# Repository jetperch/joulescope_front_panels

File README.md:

# Joulescope Front Panels

Welcome to Joulescope™ front panel hardware design project.  This project 
contains the open source hardware designs for a variety of Joulescope front
panels.  These front panels customize Joulescope so that it can more easily 
connect to your power supply and target device.
For more information on Joulescope, see 
[www.joulescope.com](https://www.joulescope.com).

As of Mar 2019, all designs were done in Autodesk Eagle PCB.

The [Baseline PDF](fp_baseline.pdf) show the board outline and critical 
dimensions.

The boards have been fabricated using PCBWay. 
Here are the order notes ([example](pcbway_order.png)):

* Size: 77.6 x 26.6 mm
* Solder Mask: Black
* Surface Finish: HASL lead free, yes to accept ENIG substitution
* Special requests: Place all markings (such as pcb order number) on back.  Add flammability rating marking, such as 94V-0.

## License

All Joulescope front-panel designs are released under the 
permissive Apache 2.0 license.

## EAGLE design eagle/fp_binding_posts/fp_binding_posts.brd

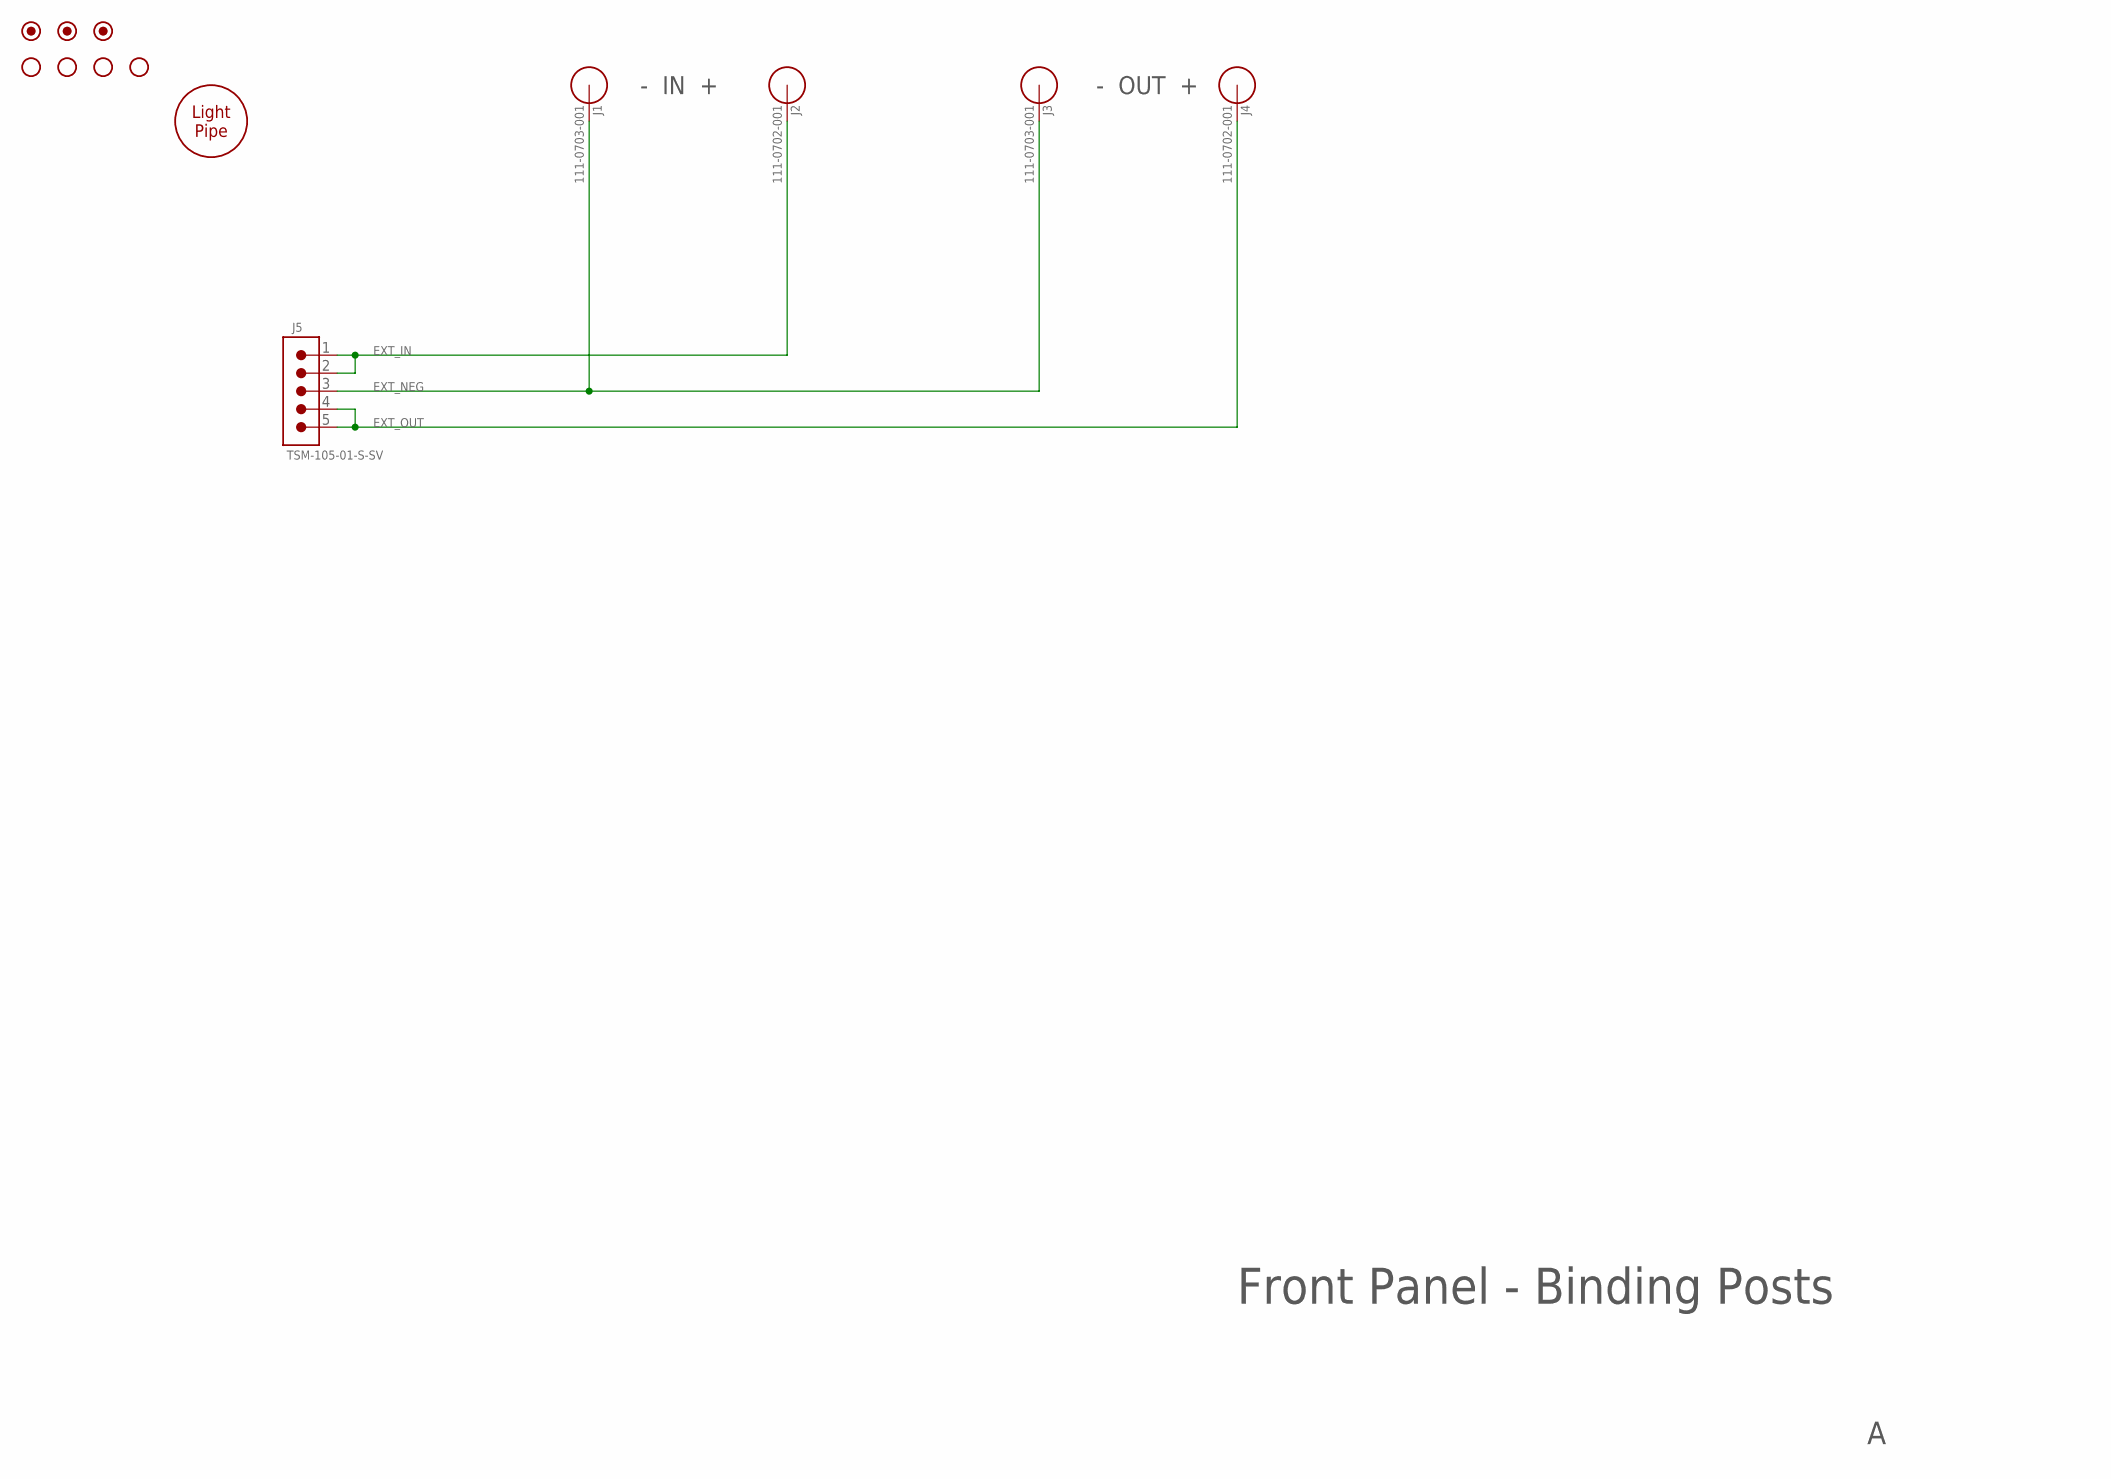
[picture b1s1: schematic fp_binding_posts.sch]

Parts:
FUD1, FUD2, FUD3: FIDUCIAL_1MM; FIDUCIAL_1MM_2MM
H1: 51513020125F; LP_3MM; MPN 51513020125F
H2, H3, H4, H5: HOLE_#6; HOLE_3.5MM
J1, J3: 111-0703-001; BINDING_POST_6
J2, J4: 111-0702-001; BINDING_POST_6
J5: TSM-105-01-S-SV; CONN_0.1_5X1_MS; MPN TSM-105-01-S-SV

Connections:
EXT_IN: J2.1, J5.1, J5.2
EXT_NEG: J1.1, J3.1, J5.3
EXT_OUT: J4.1, J5.4, J5.5

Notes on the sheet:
Front Panel - Binding Posts
- IN +
- OUT +

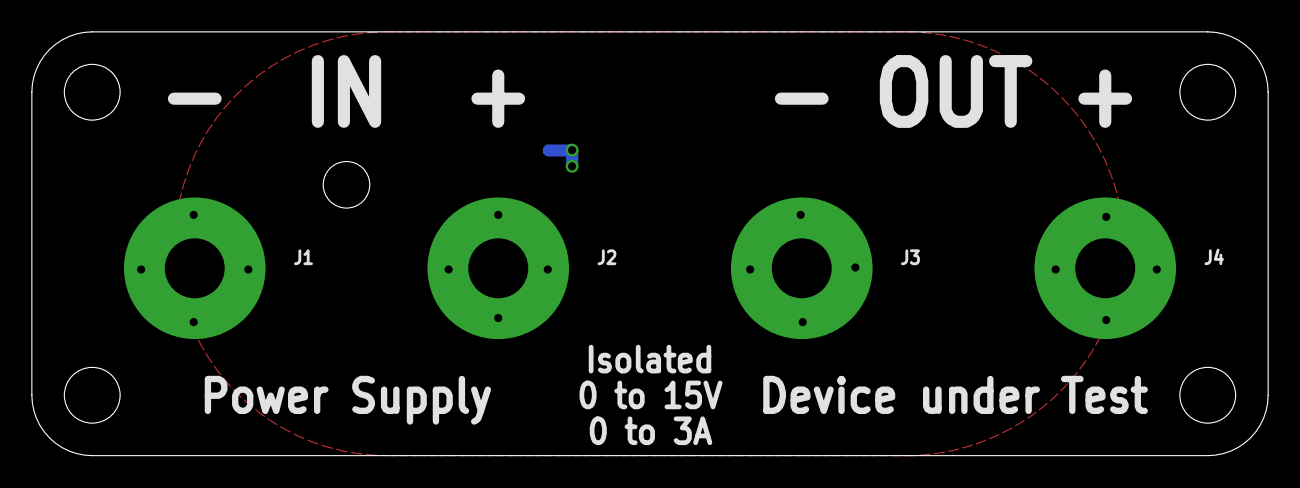
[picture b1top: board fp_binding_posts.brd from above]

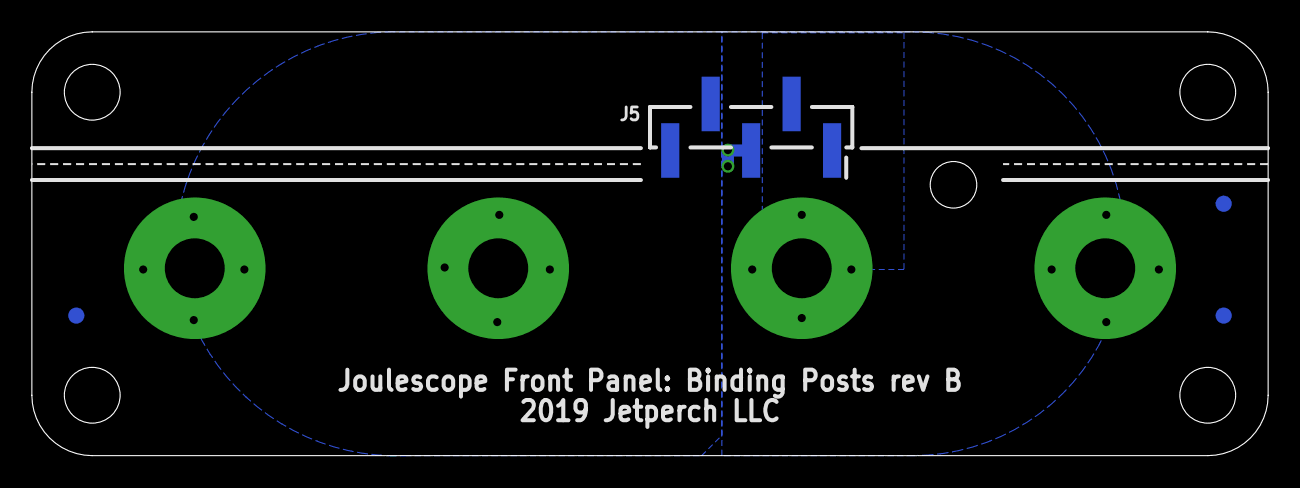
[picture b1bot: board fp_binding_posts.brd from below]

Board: 2 copper layers, 77.6 x 26.6 mm, 13 parts (4 on the bottom side), 3 nets.

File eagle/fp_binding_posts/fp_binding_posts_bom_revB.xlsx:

Binding Post Front Panel BOM - rev B
2019 June 10
# | Ref Des | Qty | Package | Description | Mfg | Mfg Part # | Notes
1 | J2, J4 | 2 |  | Binding post - red | Cinch | 111-0702-001
2 | J1, J3 | 2 |  | Binding post - black | Cinch | 111-0703-001
3 | J5 | 1 | 0.1" 1x5 SM | Surface mount header | Samtec | TSM-105-01-S-SV
4 | H1 | 1 |  | Light pipe | Dialight | 51513020125F

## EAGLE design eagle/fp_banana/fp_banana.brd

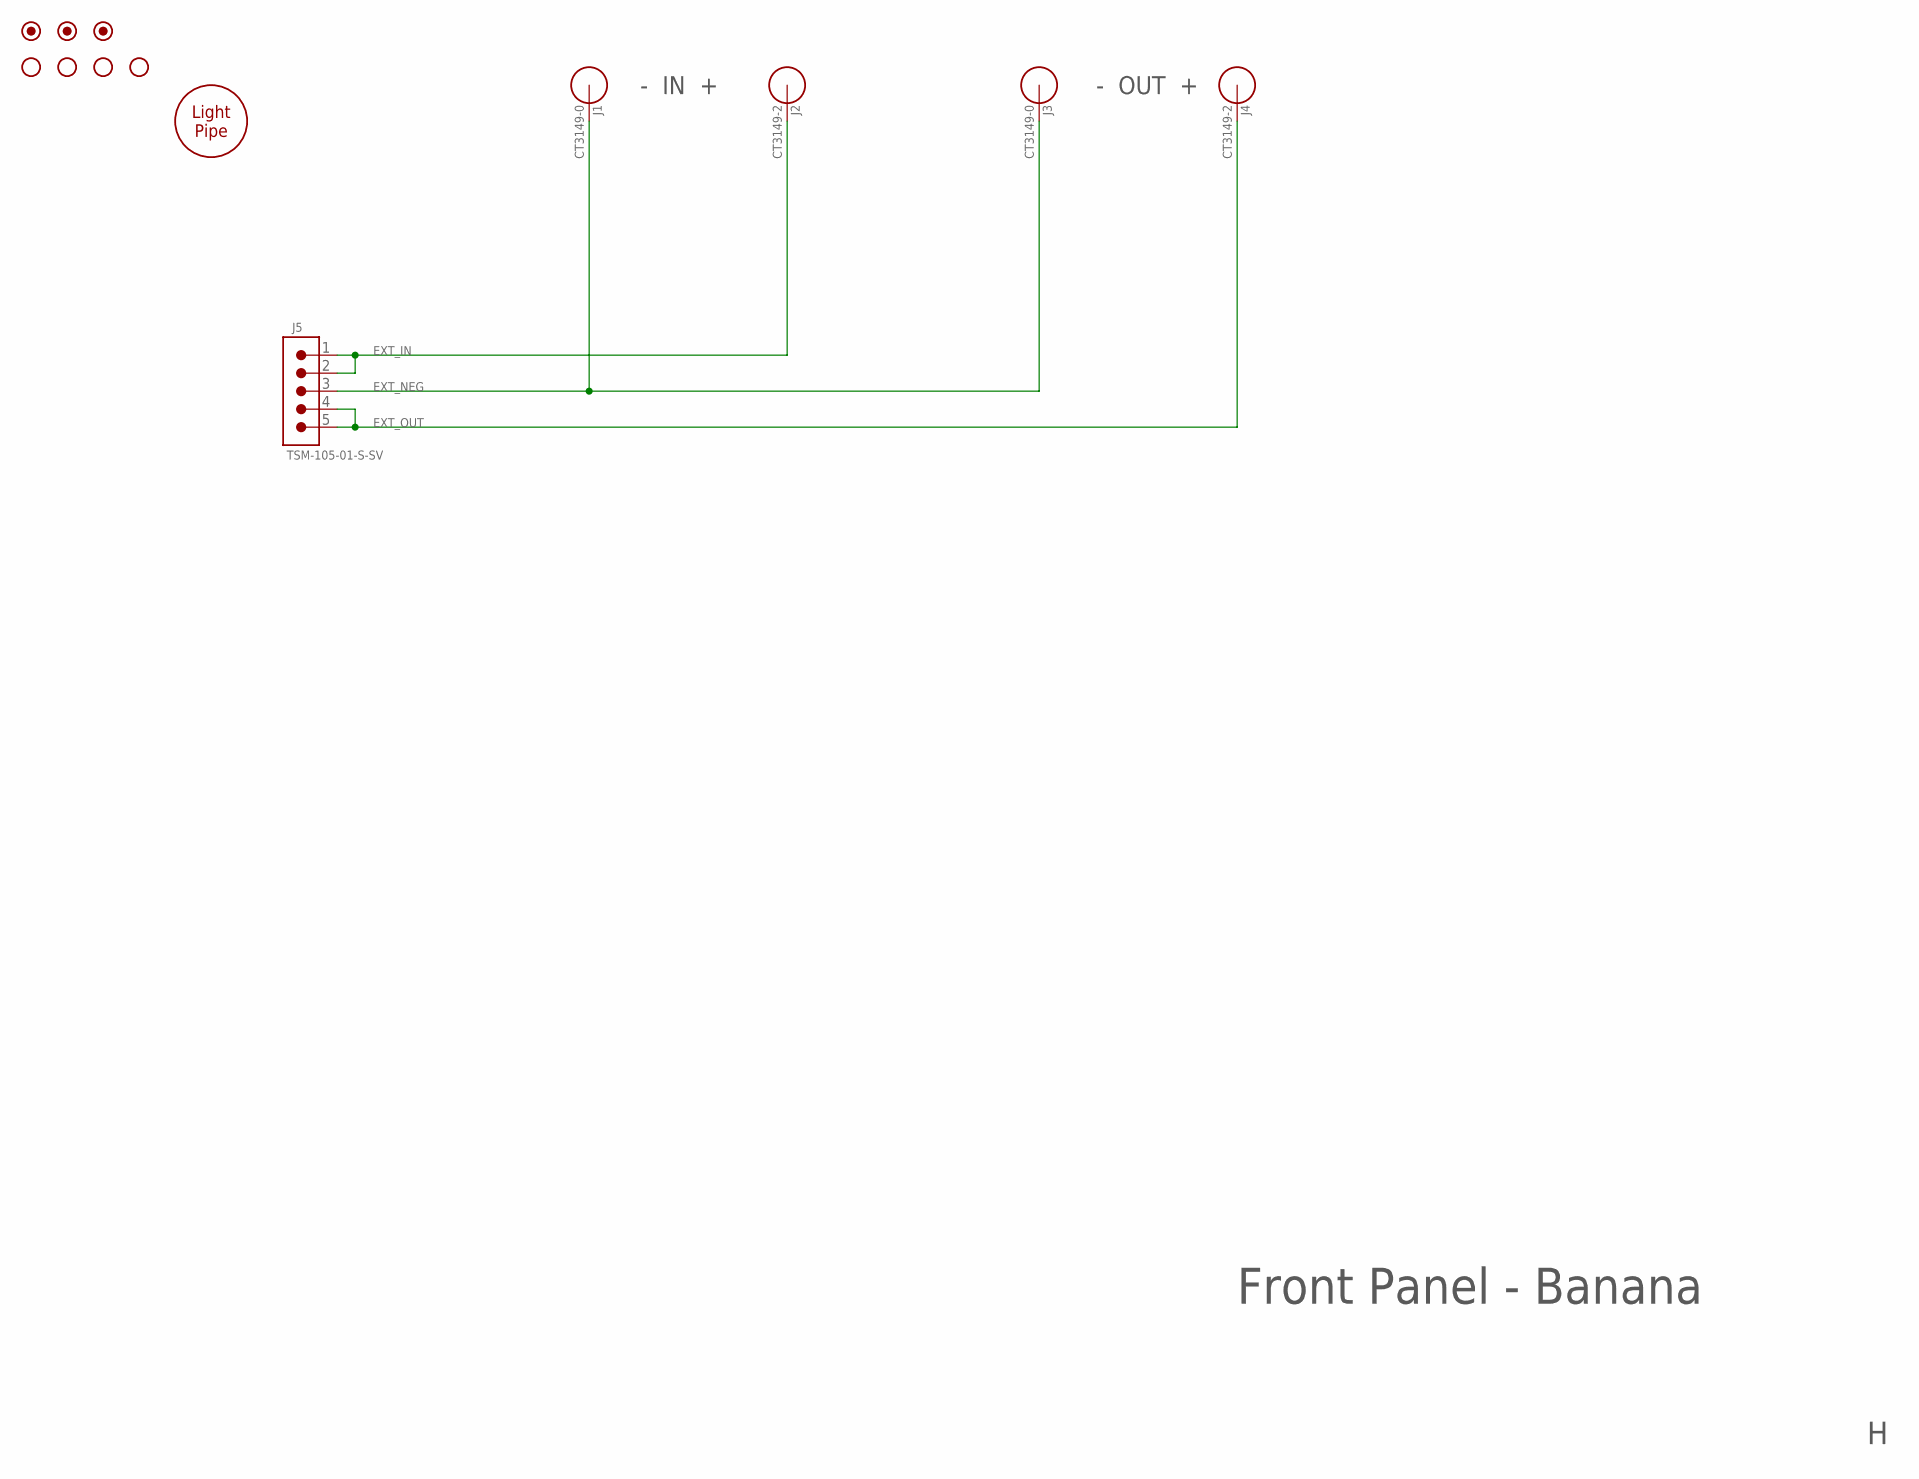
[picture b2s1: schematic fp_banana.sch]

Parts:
FUD1, FUD2, FUD3: FIDUCIAL_1MM; FIDUCIAL_1MM_2MM
H1: 51513020125F; LP_3MM; MPN 51513020125F
H2, H3, H4, H5: HOLE_#6; HOLE_3.5MM
J1, J3: CT3149-0; CT3149
J2, J4: CT3149-2; CT3149
J5: TSM-105-01-S-SV; CONN_0.1_5X1_MS; MPN TSM-105-01-S-SV

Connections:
EXT_IN: J2.A, J5.1, J5.2
EXT_NEG: J1.A, J3.A, J5.3
EXT_OUT: J4.A, J5.4, J5.5

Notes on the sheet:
Front Panel - Banana
- IN +
- OUT +

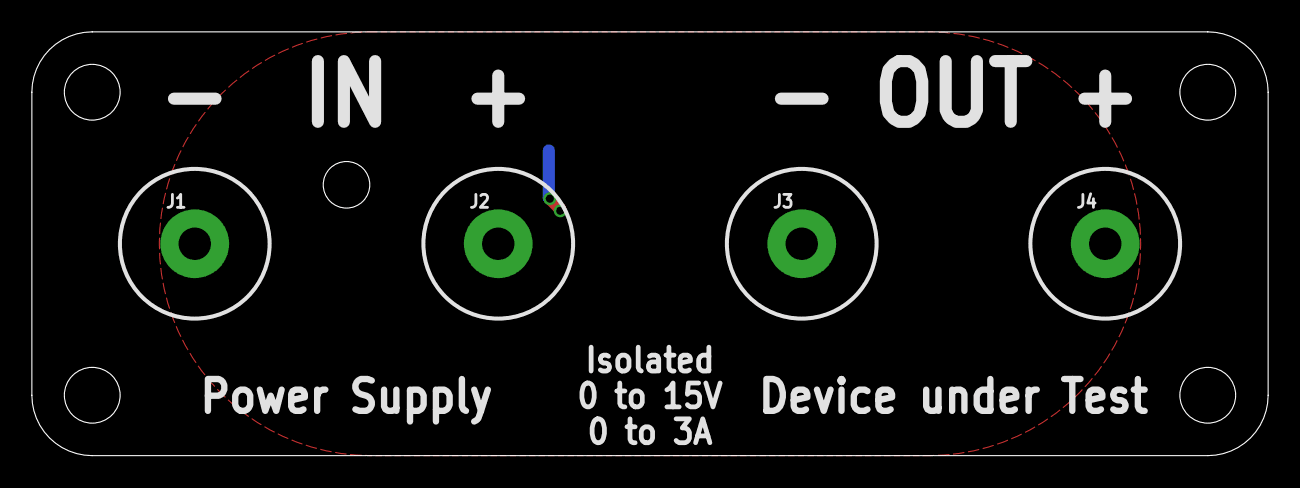
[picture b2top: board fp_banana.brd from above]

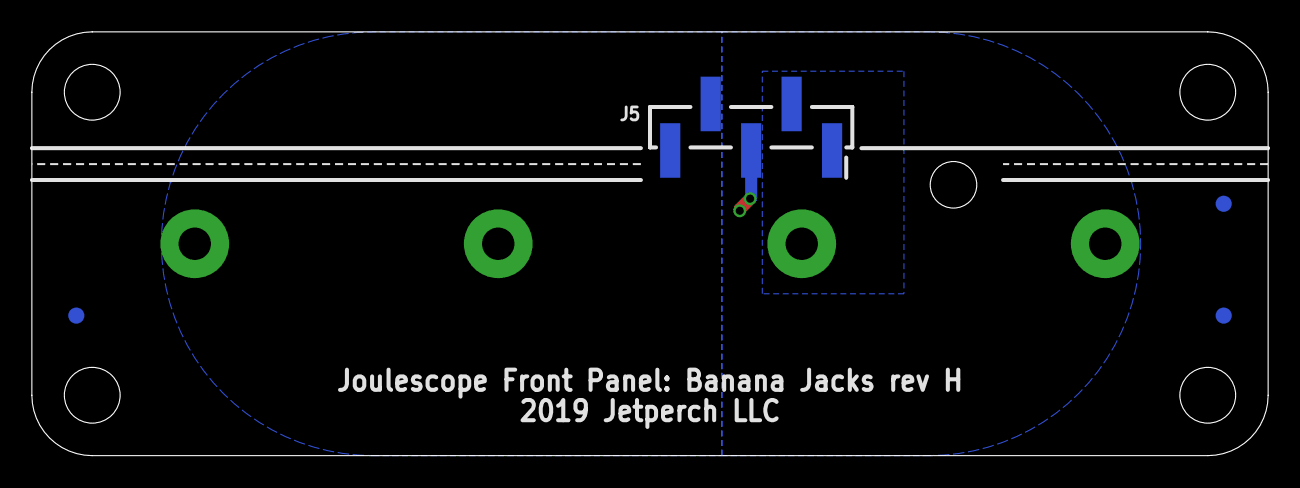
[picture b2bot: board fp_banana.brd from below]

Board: 2 copper layers, 77.6 x 26.6 mm, 13 parts (4 on the bottom side), 3 nets.

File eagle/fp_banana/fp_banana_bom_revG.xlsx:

Banana Jack Front Panel BOM - Rev G
2019 June 10
# | Ref Des | Qty | Value | Package | Description | Mfg | Mfg Part # | Notes
1 | J1, J3 | 2 |  |  | Safety banana jack - black | Cal Test | CT3149-0
2 | J2, J4 | 2 |  |  | Safety banana jack - red | Cal Test | CT3149-2
3 | J5 | 1 |  | 0.1" 1x5 SM | Surface mount header | Samtec | TSM-105-01-S-SV
4 | H1 | 1 |  |  | Light pipe | Dialight | 51513020125F
5 |  | 1 |  |  | PCB | PCBWay | W40090AXN58

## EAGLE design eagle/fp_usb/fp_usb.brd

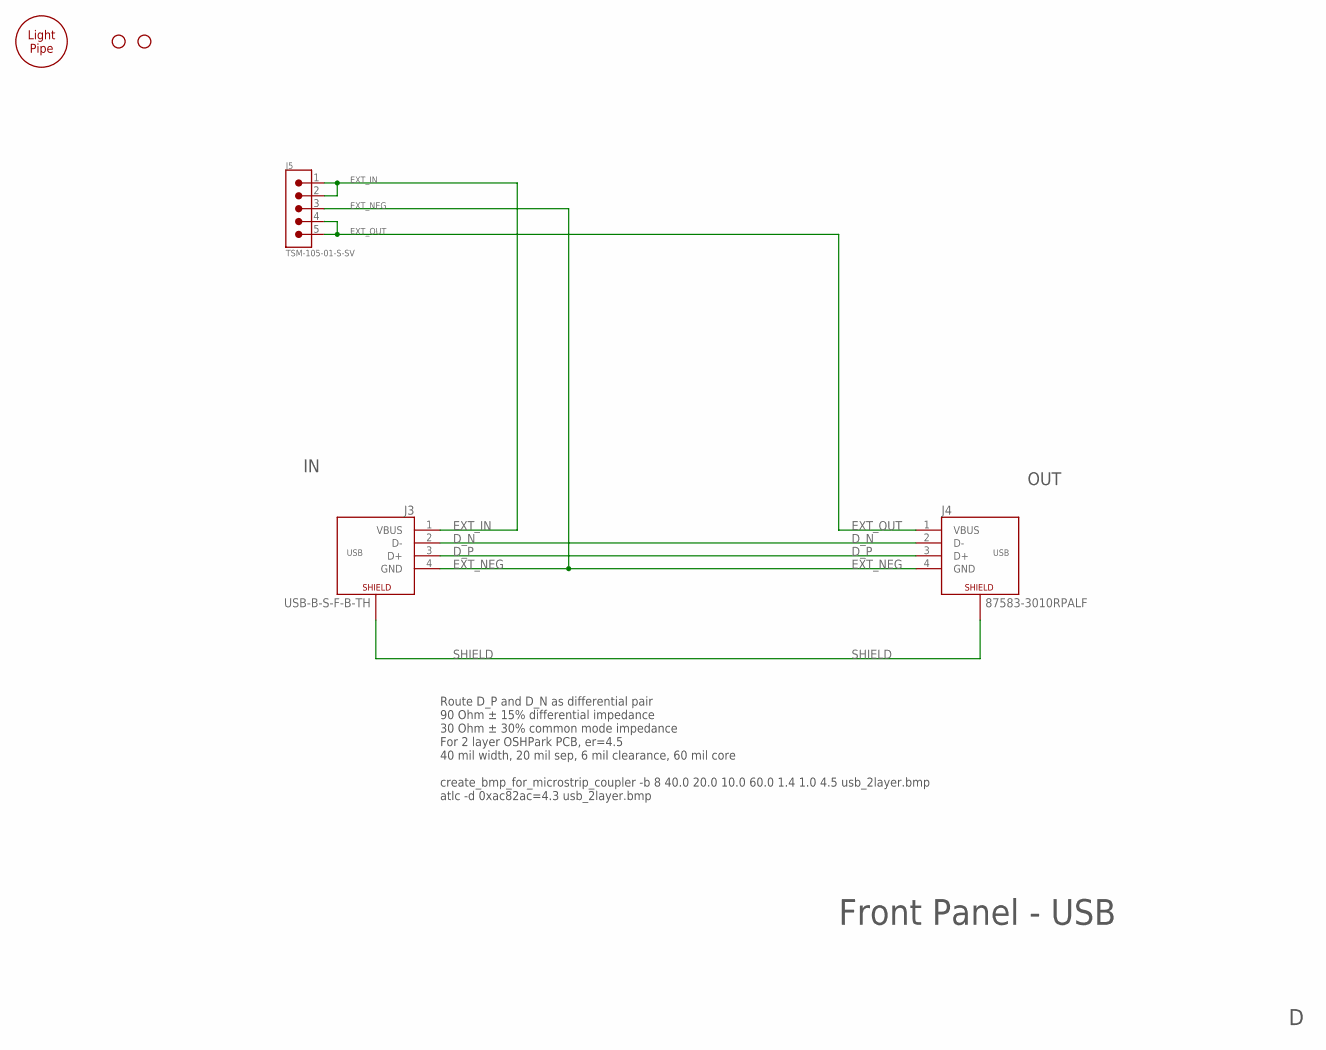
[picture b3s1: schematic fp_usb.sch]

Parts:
H1: 51513020125F; LP_3MM; MPN 51513020125F
H3, H4: HOLE_#6; HOLE_3.5MM
J3: USB-B-S-F-B-TH; USB-B-TH; MPN USB-B-S-F-B-TH
J4: 87583-3010RPALF; USB-A_RPCT; MPN 87583-3010RPALF
J5: TSM-105-01-S-SV; CONN_0.1_5X1_MS; MPN TSM-105-01-S-SV

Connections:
D_N: J3.2 (D-), J4.2 (D-)
D_P: J3.3 (D+), J4.3 (D+)
EXT_IN: J3.1 (VBUS), J5.1, J5.2
EXT_NEG: J3.4 (GND), J4.4 (GND), J5.3
EXT_OUT: J4.1 (VBUS), J5.4, J5.5
SHIELD: J3.SHIELD@1 (SHIELD), J3.SHIELD@2 (SHIELD), J4.SHIELD@1 (SHIELD), J4.SHIELD@2 (SHIELD)

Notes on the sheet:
Front Panel - USB
OUT
Route D_P and D_N as differential pair 90 Ohm ± 15% differential impedance 30 Ohm ± 30% common mode impedance For 2 layer OSHPark PCB, er=4.5 40 mil width, 20 mil sep, 6 mil clearance, 60 mil core create_bmp_for_microstrip_coupler -b 8 40.0 20.0 10.0 60.0 1.4 1.0 4.5 usb_2layer.bmp atlc -d 0xac82ac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

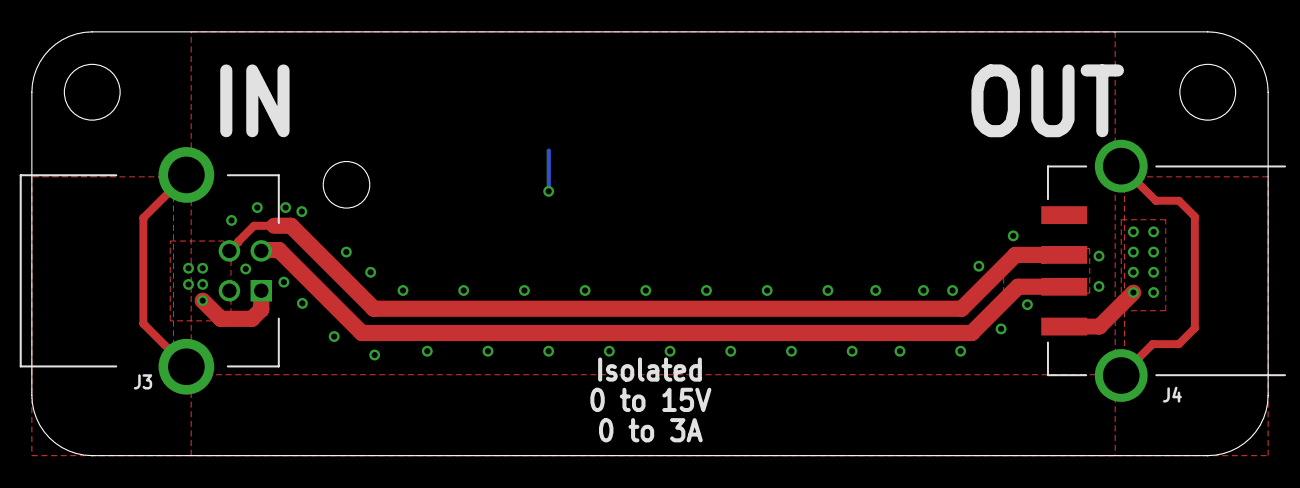
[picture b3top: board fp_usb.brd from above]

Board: 2 copper layers, 77.6 x 26.6 mm, 6 parts (1 on the bottom side), 6 nets.

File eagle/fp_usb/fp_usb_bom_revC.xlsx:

USB Front Panel BOM - rev C
2019 June 10
# | Ref Des | Qty | Value | Package | Description | Mfg | Mfg Part # | Notes
1 | J5 | 1 |  | 0.1" 1x5 SM | Surface mount header | Samtec | TSM-105-01-S-SV
2 | J3 | 1 |  |  | USB B connector | Samtec | USB-B-S-F-B-TH
3 | J4 | 1 |  |  | USB A connector | Amphenol | 87583-3010RPALF
4 | H1 | 1 |  |  | Light Pipe | Dialight | 51513020125F

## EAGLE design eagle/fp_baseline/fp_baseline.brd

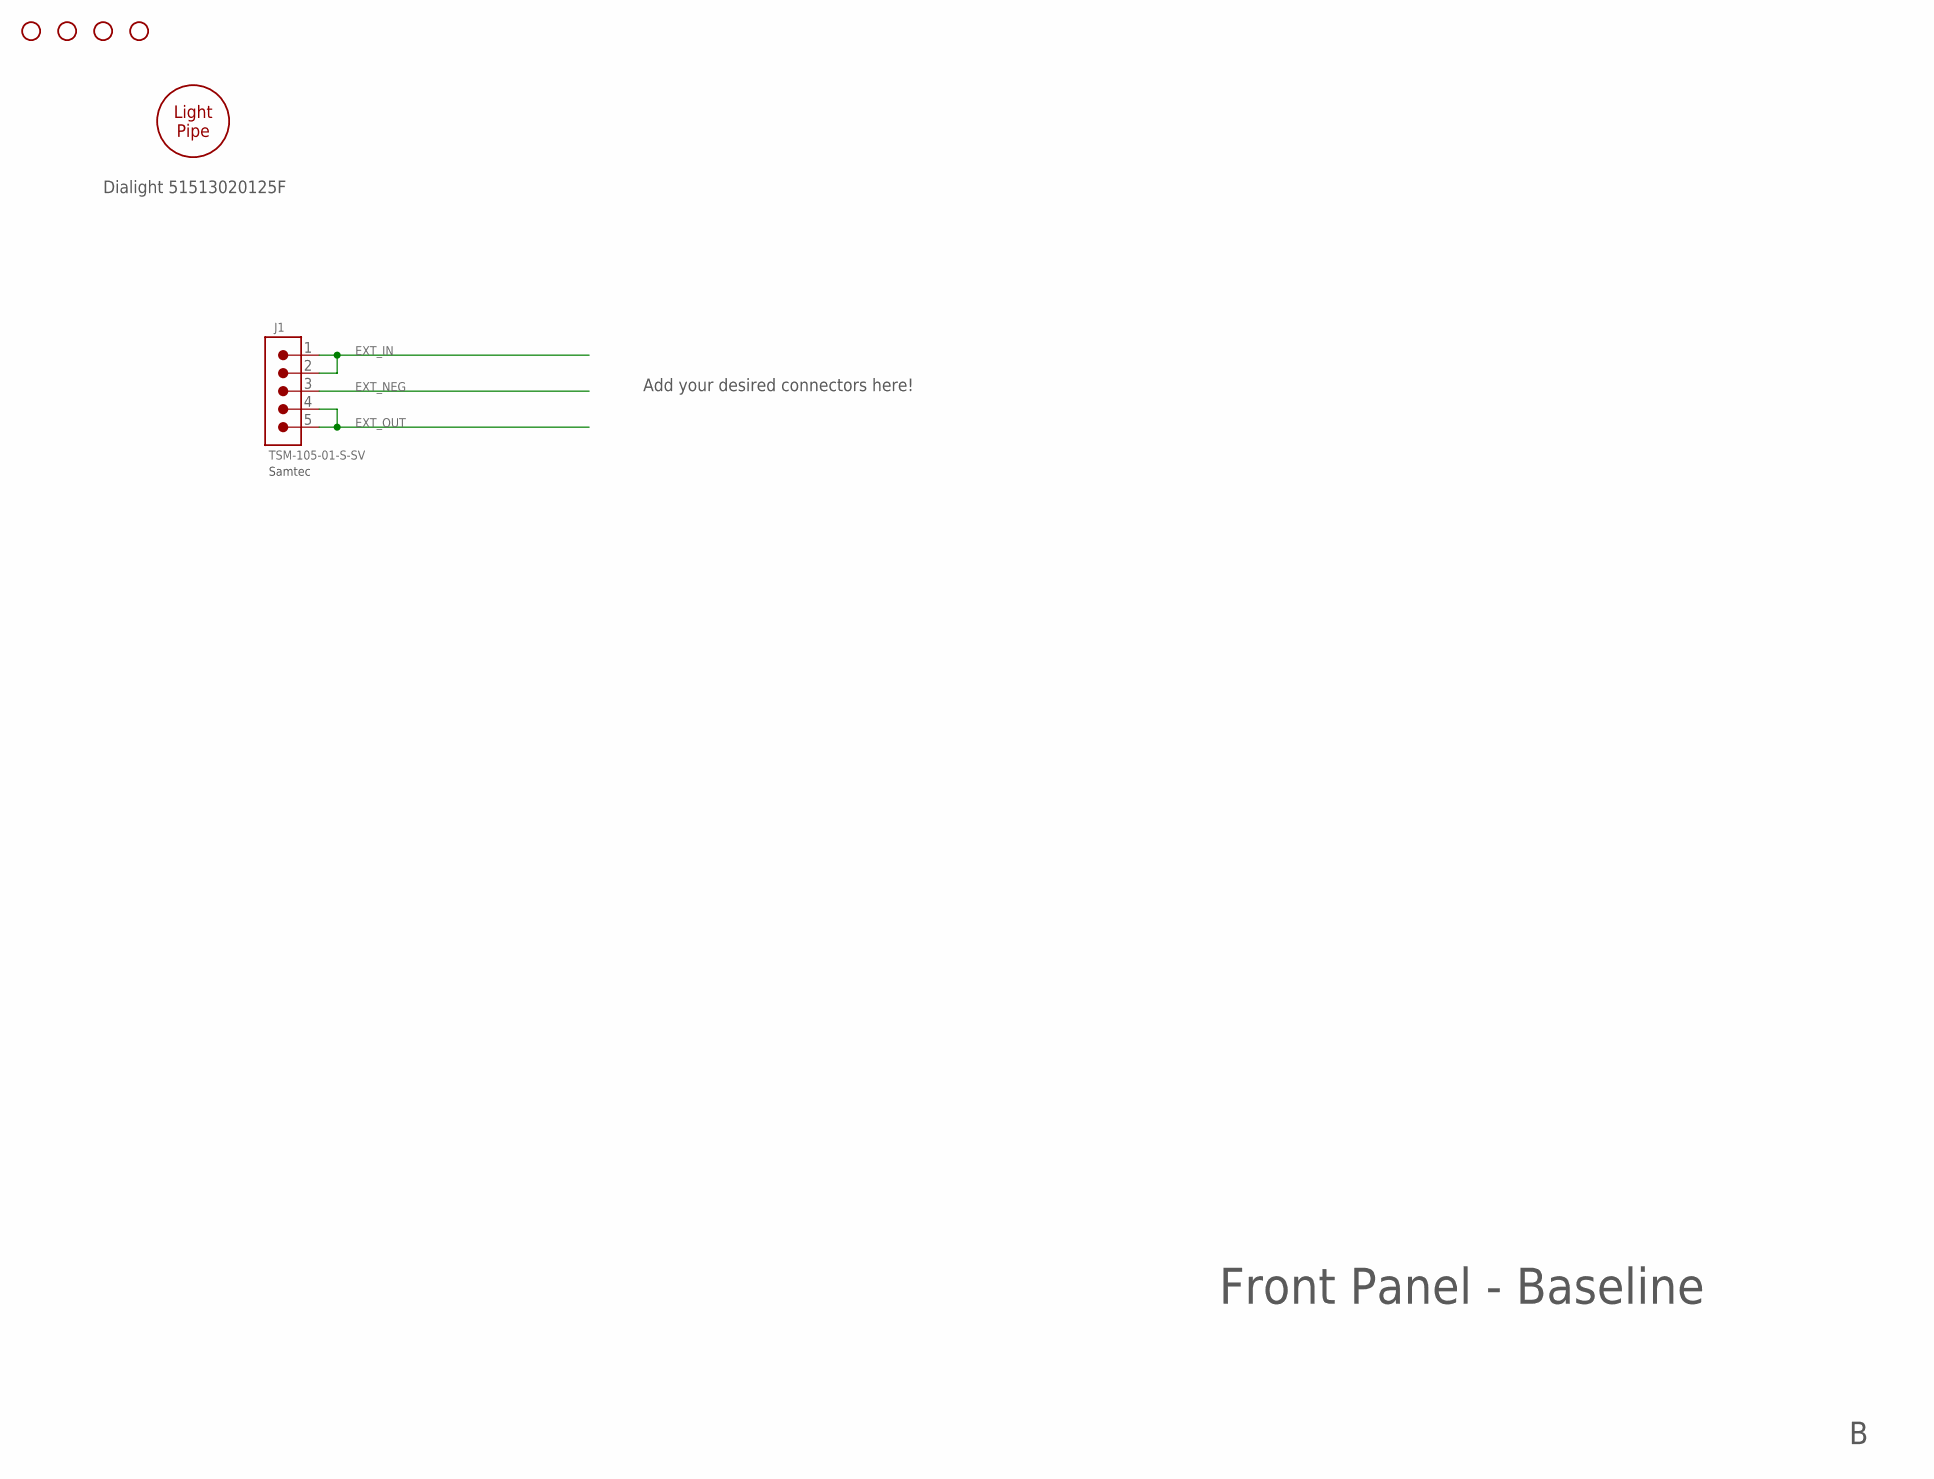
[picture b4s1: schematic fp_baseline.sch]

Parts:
H1: 51513020125F; LP_3MM; MPN 51513020125F
H2, H3, H4, H5: HOLE_#6; HOLE_3.5MM
J1: TSM-105-01-S-SV; CONN_0.1_5X1_MS; MPN TSM-105-01-S-SV

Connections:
EXT_IN: J1.1, J1.2
EXT_NEG: J1.3
EXT_OUT: J1.4, J1.5

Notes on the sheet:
Front Panel - Baseline
Add your desired connectors here!
Dialight 51513020125F
Samtec

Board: 2 copper layers, 6 parts (1 on the bottom side), 2 nets.

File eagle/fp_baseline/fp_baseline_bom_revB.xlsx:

Baseline Front Panel BOM - Rev B
2019 Aug 12
# | Ref Des | Qty | Value | Package | Description | Mfg | Mfg Part # | Notes
1 | J1 | 1 |  | 0.1" 1x5 SM | Surface mount header | Samtec | TSM-105-01-S-SV
2 | H1 | 1 |  |  | Light pipe | Dialight | 51513020125F
3 | PCB | 1 |  |  | PCB

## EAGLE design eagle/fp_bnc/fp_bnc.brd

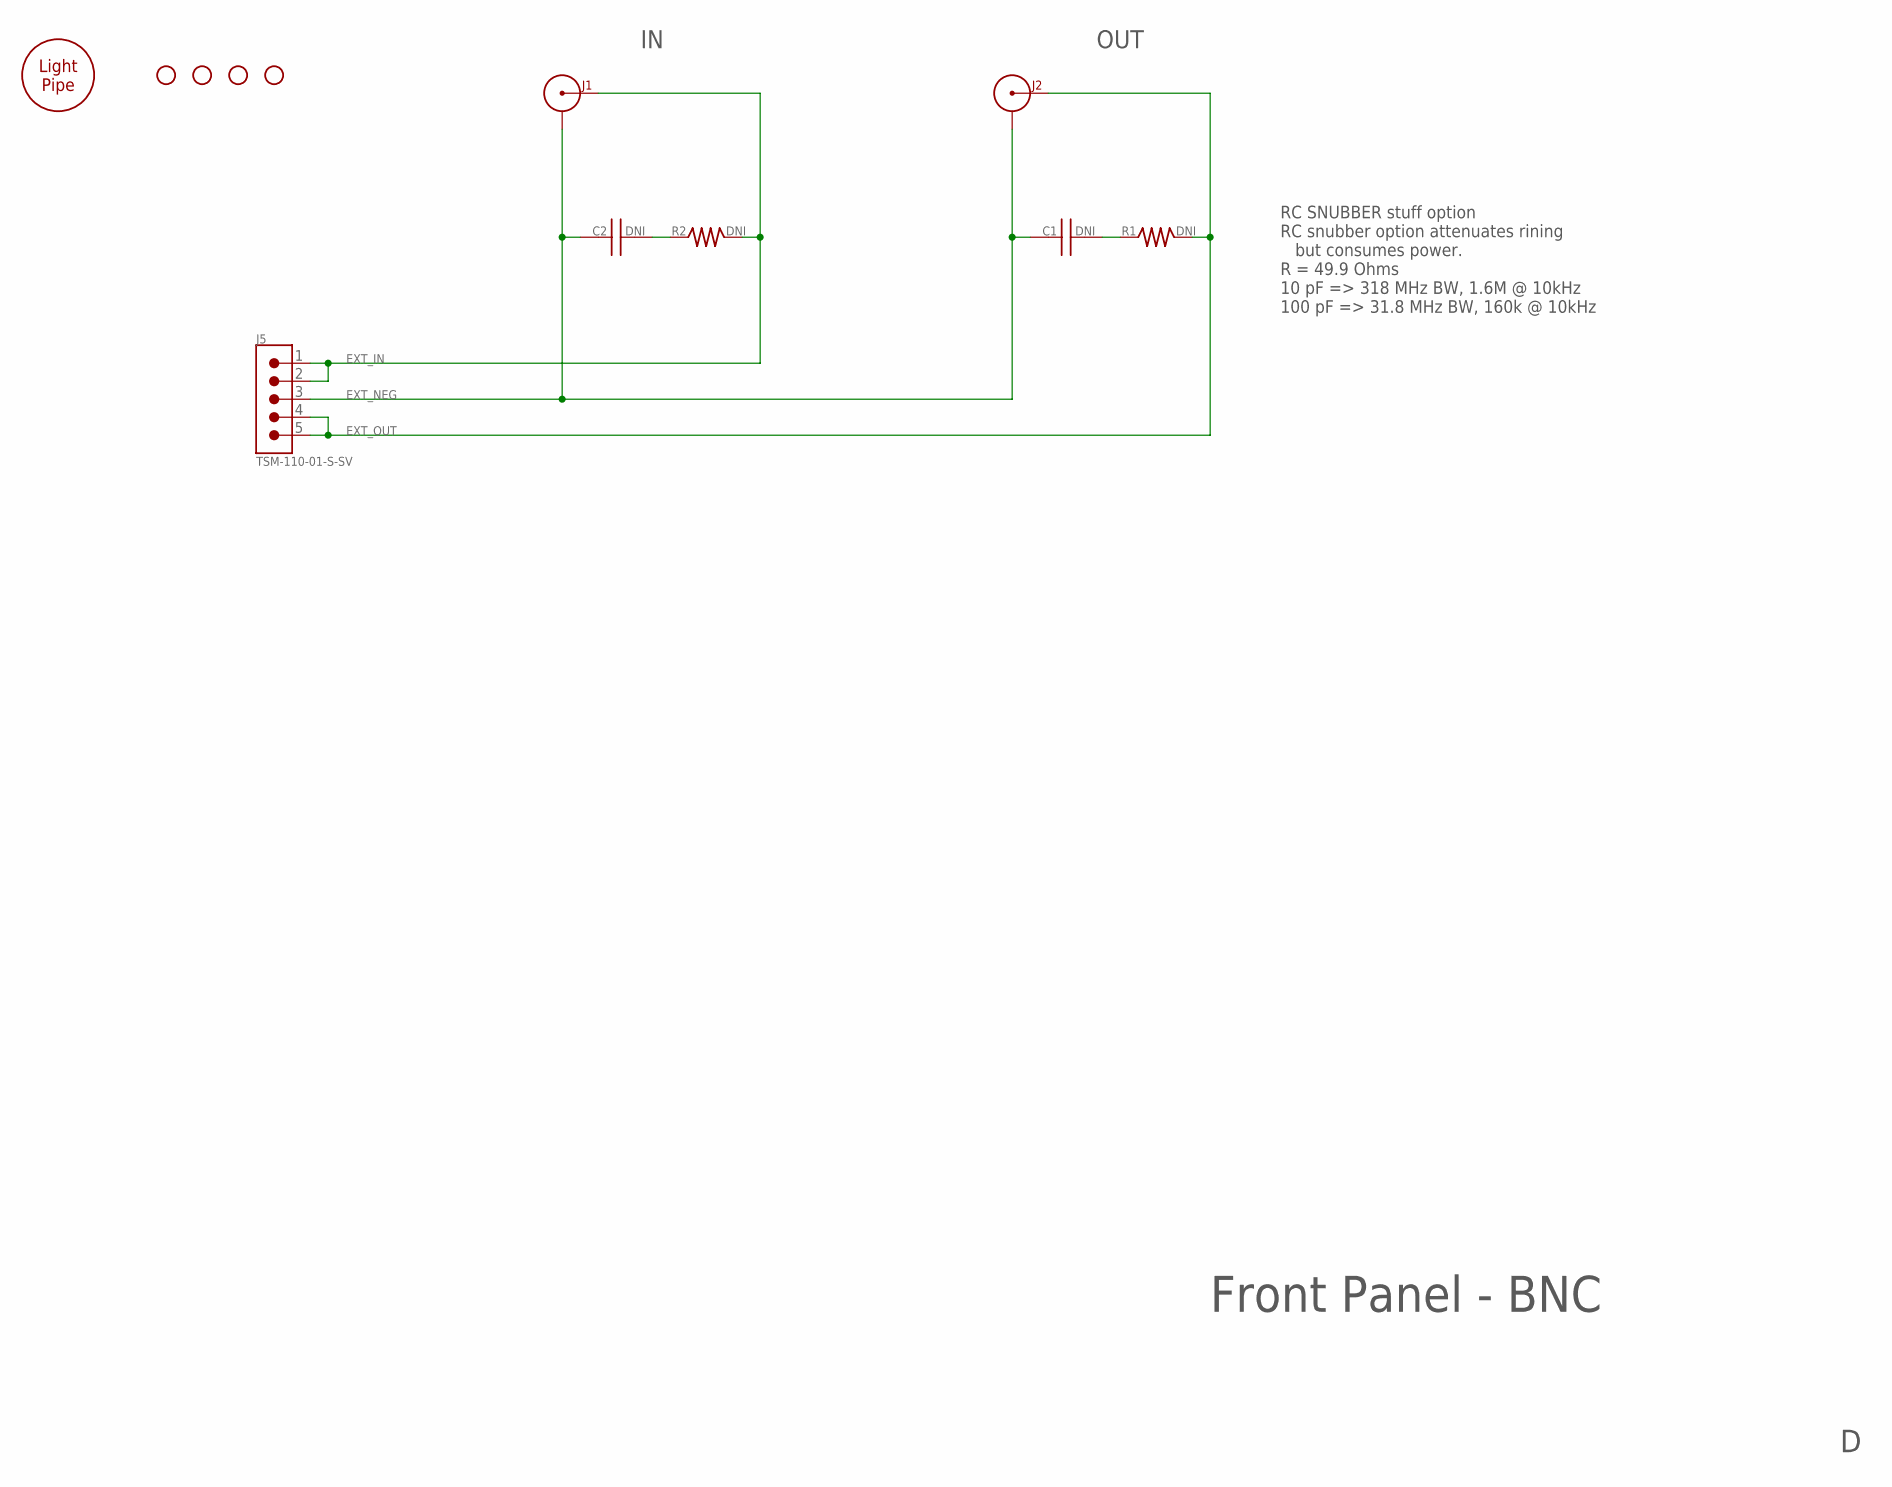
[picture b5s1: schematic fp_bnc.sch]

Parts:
C1, C2: DNI; 0603
H1: 51513020125F; LP_3MM; MPN 51513020125F
H2, H3, H4, H5: HOLE_#6; HOLE_3.5MM
J1, J2: 031-5329-52RFX; BNC_31-5329-52RFX; MPN 031-5329-52RFX
J5: TSM-110-01-S-SV; CONN_0.1_5X1_MS; MPN TSM-110-01-S-SV
R1, R2: DNI; 1206

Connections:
EXT_IN: J1.SIGNAL, J5.1, J5.2, R2.2
EXT_NEG: C1.1, C2.1, J1.G@1 (SHIELD), J1.G@2 (SHIELD), J1.G@3 (SHIELD), J1.G@4 (SHIELD), J2.G@1 (SHIELD), J2.G@2 (SHIELD), J2.G@3 (SHIELD), J2.G@4 (SHIELD), J5.3
EXT_OUT: J2.SIGNAL, J5.4, J5.5, R1.2
unnamed: C2.2, R2.1
unnamed: C1.2, R1.1

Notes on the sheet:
Front Panel - BNC
OUT
RC SNUBBER stuff option RC snubber option attenuates rining but consumes power. R = 49.9 Ohms 10 pF => 318 MHz BW, 1.6M @ 10kHz 100 pF => 31.8 MHz BW, 160k @ 10kHz

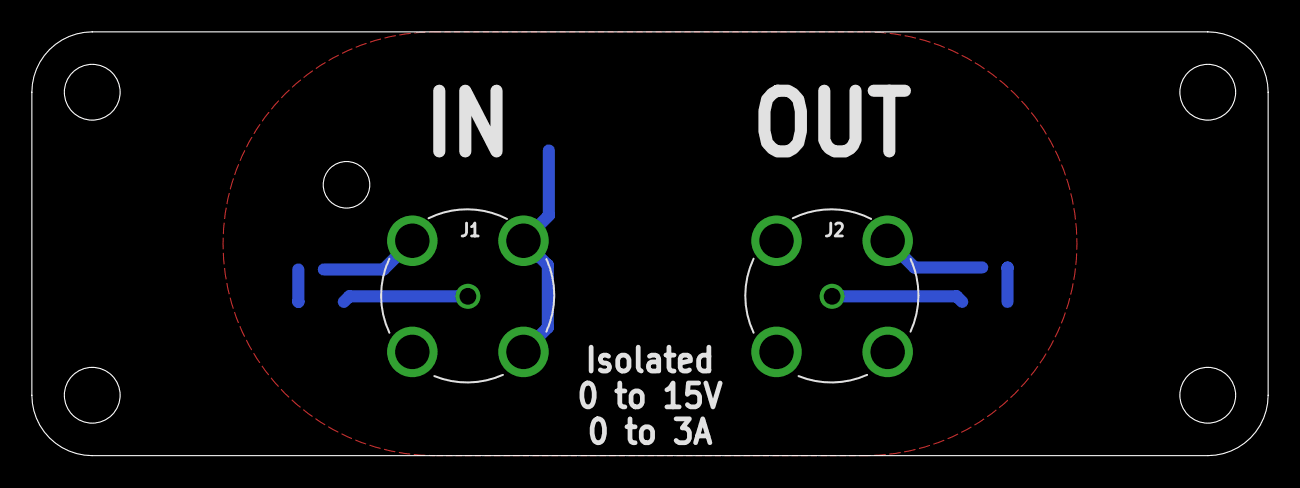
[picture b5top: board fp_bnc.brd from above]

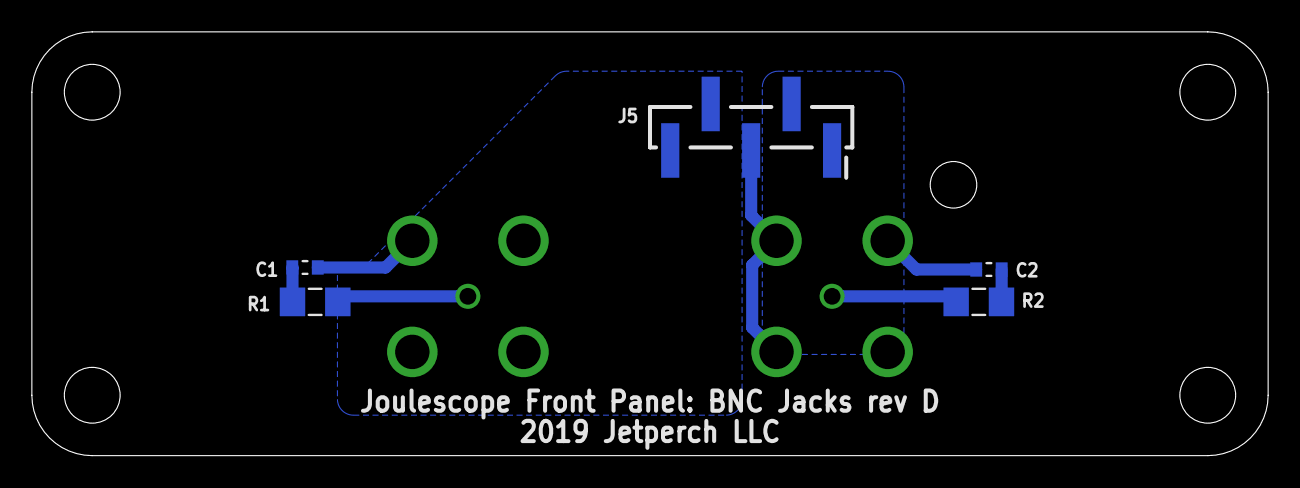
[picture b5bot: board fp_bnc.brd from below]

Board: 2 copper layers, 77.6 x 26.6 mm, 12 parts (5 on the bottom side), 5 nets.

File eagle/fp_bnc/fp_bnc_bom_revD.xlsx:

BNC Front Panel BOM - revD
2019 June 10
# | Ref Des | Qty | Value | Package | Description | Mfg | Mfg Part # | Notes
1 | J1, J2 | 2 |  |  | BNC connector | Amphenol | 031-5329-52RFX
2 | J5 | 1 |  |  | Surface mount header | Samtec | TSM-110-01-S-SV
3 | H1 | 1 |  |  | Light Pipe | Dialight | 51513020125F

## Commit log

2019-01-25 Initial public commit.
2019-01-27 Improved README slightly.
2019-03-19 Added binding posts front panel, updated baseline, and published baseline PDF.
2019-03-20 Fixed backside keepout (in blue) so that it does not hide the rounded corners.
2019-03-20 Clarified that blue is the backside keepout.
2019-04-16 Pre-production update.
    * Increased clearances from chassis/enclosure ground.
    * Improved text.
    * Added gerbers.
    * Added USB back panel.
2019-04-16 Added PCBWay order notes to readme.
2019-04-16 Updated fp_baseline edit date.
2019-05-09 Modified USB back panel to move GPI/O cutout and fixed schematic file name.
2019-07-30 Updated baseline to clarify dimensions, placement and part numbers.
2019-07-30 Added BOMs.
2019-07-30 Added PDFs for fp_usb schematic and layout.
2019-08-12 Updated baseline front panel design.
    * Added gerbers
    * Added BOM
    * Added "Rev B" text to brd file.
2019-08-13 Initial Kicad baseline front panel files commit
2019-08-13 Fixed eagle/fp_usb mounting hole location which was off by 0.18 mm (7 mil).
2019-08-13 Ignore KiCAD backup and cache files and removed from pull request.
2019-09-15 Added brief fab notes to back panel PCB design.
2019-09-15 Banana Jack front panel rev H
    * Increased 5x1 connector pad width from 45 mil to 50 mil.
    * Added brief fab notes & fab drawing.
    * Improved dimensioning for clarity.
    * Removed excessive number of EXT_NEG vias.
2019-10-21 Fixed binding post centerline offset dimension.
2020-07-07 Added fp_usb3 gerber design. Thank you Mettler-Toledo AutoChem!
